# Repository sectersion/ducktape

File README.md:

# ducktape

**ducktape** is a budget-friendly, fully open alternative to the USB Rubber ducky, the well-known keystroke-injection tool used in cybersecurity and physical pentesting.  
The goal: COST OPTIMIZATION

Instead of hiding behind proprietary hardware, ducktape uses simple off-the-shelf parts and a dead-simple design you can understand, repair, and modify. Cheap to build, easy to hack on, and perfect for learning physical security without dropping triple digits on a dongle.

I built this because I’m diving deeper into physical access testing, and I refuse to pay luxury-brand prices for tools that are essentially microcontrollers pretending to be premium gear.  
Companies like Flipper and Hak5 make cool stuff — sure — but most of it can be recreated for a fraction of the price if you’re willing to solder and tinker.

## Schematic

## PCB

## 3D Model

## Disclaimer
This project is for **educational and authorized security testing only**.  
You’re responsible for how you use it.  
If you plug this into a device you don’t have explicit permission to test, that’s on you, not me, not the repo, not the PCB.

Pentest ethically.

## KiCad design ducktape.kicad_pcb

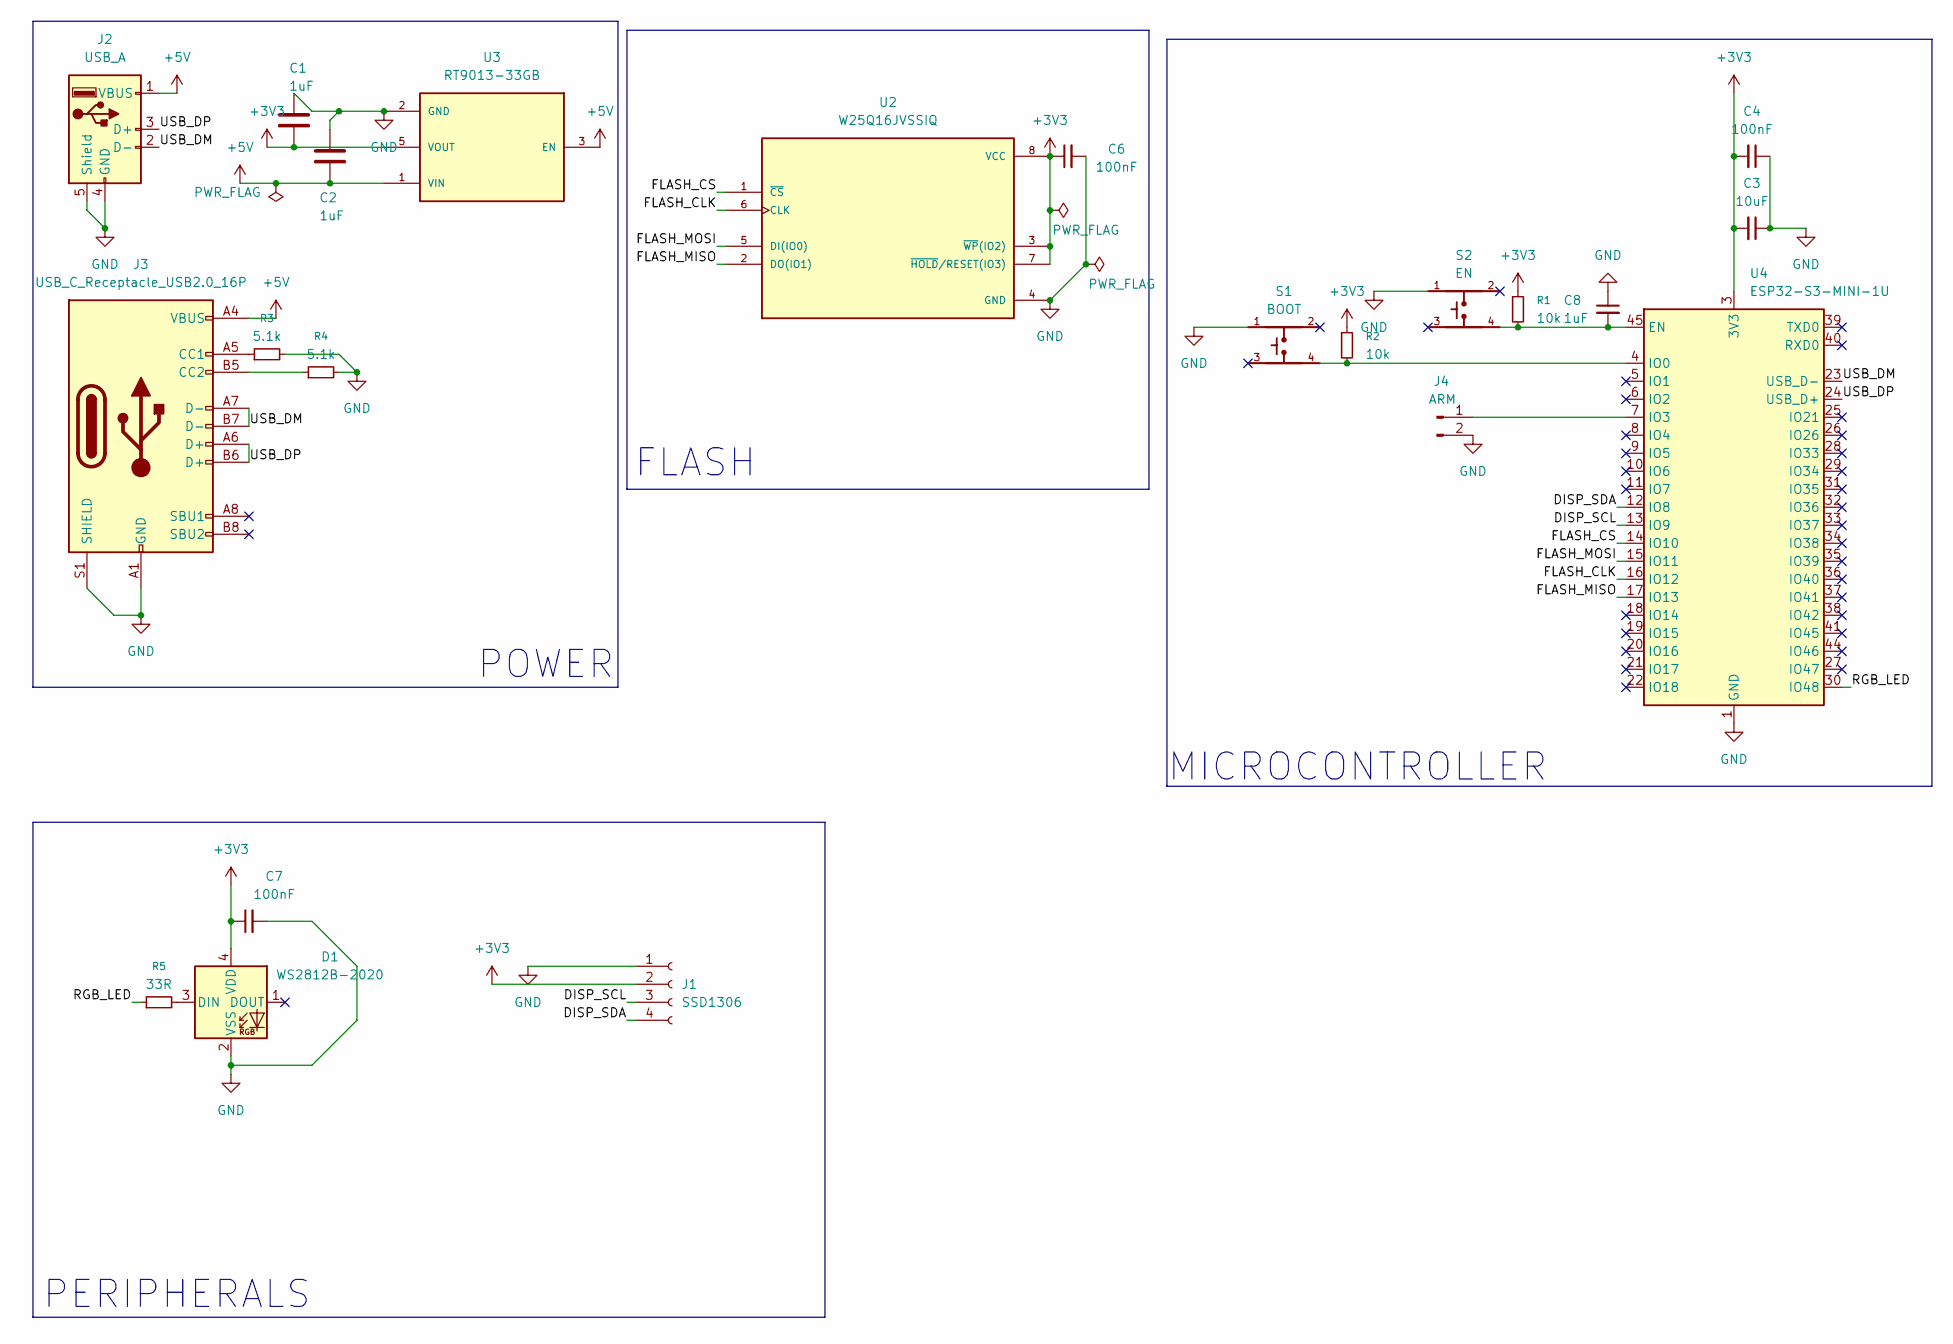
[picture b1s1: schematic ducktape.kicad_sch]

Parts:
C1, C2, C8: 1uF; C_0402_1005Metric
C3: 10uF; C_0402_1005Metric
C4, C6, C7: 100nF; C_0402_1005Metric
D1: WS2812B-2020; LED_WS2812B-2020_PLCC4_2.0x2.0mm
J1: SSD1306; PinSocket_1x04_P2.54mm_Vertical
J2: USB_A; USB_A_CNCTech_1001-011-01101_Horizontal
J3: USB_C_Receptacle_USB2.0_16P; USB_C_Receptacle_HRO_TYPE-C-31-M-12
J4: ARM; PinHeader_1x02_P2.54mm_Vertical
R1, R2: 10k; R_0402_1005Metric
R3, R4: 5.1k; R_0402_1005Metric
R5: 33R; R_0402_1005Metric
S1: BOOT; SW_SKRPACE010
S2: EN; SW_SKRPACE010
U2: W25Q16JVSSIQ; SOIC127P790X216-8N
U3: RT9013-33GB; SOT94P279X129-5N; PARTREV Aprill 2011
U4: ESP32-S3-MINI-1U; ESP32-S2-MINI-1U

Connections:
+3V3: C1.2, C3.2, C4.2, C6.1, C7.1, D1.4 (VDD), J1.2, R1.1, R2.1, U2.3 (~WP(IO2)), U2.7 (~HOLD/RESET(IO3)), U2.8 (VCC), U3.5 (VOUT), U4.3 (3V3)
+5V: C2.2, J2.1 (VBUS), J3.A4 (VBUS), J3.A9 (VBUS), J3.B4 (VBUS), J3.B9 (VBUS), U3.1 (VIN), U3.3 (EN)
/DISP_SCL: J1.3, U4.13 (IO9)
/DISP_SDA: J1.4, U4.12 (IO8)
/FLASH_CLK: U2.6 (CLK), U4.16 (IO12)
/FLASH_CS: U2.1 (~CS), U4.14 (IO10)
/FLASH_MISO: U2.2 (DO(IO1)), U4.17 (IO13)
/FLASH_MOSI: U2.5 (DI(IO0)), U4.15 (IO11)
/RGB_LED: R5.1, U4.30 (IO48)
/USB_DM: J2.2 (D-), J3.A7 (D-), J3.B7 (D-), U4.23 (USB_D-)
/USB_DP: J2.3 (D+), J3.A6 (D+), J3.B6 (D+), U4.24 (USB_D+)
GND: C1.1, C2.1, C3.1, C4.1, C6.2, C7.2, C8.1, D1.2 (VSS), J1.1, J2.4 (GND), J2.5 (Shield), J3.A1 (GND), J3.A12 (GND), J3.B1 (GND), J3.B12 (GND), J3.S1 (SHIELD), J4.2, R3.2, R4.2, S1.1, S2.1, U2.4 (GND), U3.2 (GND), U4.1 (GND), U4.2 (GND), U4.42 (GND), U4.43 (GND), U4.46 (GND), U4.47 (GND), U4.48 (GND), U4.49 (GND), U4.50 (GND), U4.51 (GND), U4.52 (GND), U4.53 (GND), U4.54 (GND), U4.55 (GND), U4.56 (GND), U4.57 (GND), U4.58 (GND), U4.59 (GND), U4.60 (GND), U4.61 (GND), U4.62 (GND), U4.63 (GND), U4.64 (GND), U4.65 (GND)
unnamed: D1.3 (DIN), R5.2
unnamed: J3.A5 (CC1), R3.1
unnamed: J3.B5 (CC2), R4.1
unnamed: J4.1, U4.7 (IO3)
unnamed: C8.2, R1.2, S2.4, U4.45 (EN)
unnamed: R2.2, S1.4, U4.4 (IO0)

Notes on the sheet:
PERIPHERALS
MICROCONTROLLER
POWER
FLASH

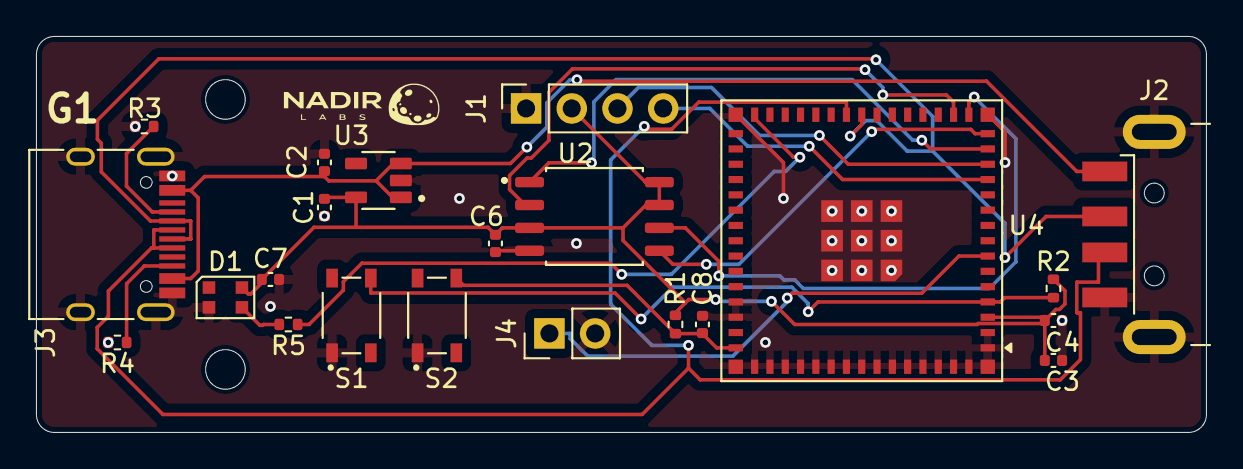
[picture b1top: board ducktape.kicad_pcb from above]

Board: 2 copper layers, 65.0 x 22.0 mm, 25 parts (0 on the bottom side), 18 nets.

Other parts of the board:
G1: LOGO; nl_bw
REF1, REF1#2: MountingHole_2.2mm_M2

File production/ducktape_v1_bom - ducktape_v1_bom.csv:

Designator,Footprint,Quantity,Value,LCSC Part #
"C1, C2, C8",0402,3,1uF,C14445
C3,0402,1,10uF,C315248
"C4, C6, C7",0402,3,100nF,C77020
D1,LED_WS2812B-2020_PLCC4_2.0x2.0mm,1,WS2812B-2020,C965555
J1,PinSocket_1x04_P2.54mm_Vertical,1,SSD1306,C2718488
J2,USB_A_CNCTech_1001-011-01101_Horizontal,1,USB_A,C2943127
J3,USB_C_Receptacle_HRO_TYPE-C-31-M-12,1,USB_C_Receptacle_USB2.0_16P,C165948
J4,PinHeader_1x02_P2.54mm_Vertical,1,ARM,C42431798
"R1, R2",0402,2,10k,C60490
"R3, R4",0402,2,5.1k,C105872
R5,0402,1,33R,C138002
S1,SW_SKRPACE010,1,BOOT,C139797
S2,SW_SKRPACE010,1,EN,C139797
U2,SOIC127P790X216-8N,1,W25Q16JVSSIQ,C131025
U3,SOT94P279X129-5N,1,RT9013-33GB,C47773
U4,ESP32-S2-MINI-1U,1,ESP32-S3-MINI-1U,C2980299

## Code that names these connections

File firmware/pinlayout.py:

from machine import Pin

# display pin assignments
DISP_SDA = Pin(8)   # data
DISP_SCL = Pin(9)   # clock

#flash pins
FLASH_CS = Pin(10)
FLASH_MOSI = Pin(11)
FLASH_CLK = Pin(12)
FLASH_MISO = Pin(13)

#led
RGB_LED = Pin(48)

#arm header
ARM = Pin(3, Pin.IN, Pin.PULL_UP)

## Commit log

2026-03-23 feat: schematic in one sitting
2026-03-24 finish pcb and generate gerbers
2026-03-25 finish PCB and export 3d model
2026-03-25 Create README.md for ducktape project
    Add README.md for ducktape project with details on its purpose, design, and usage.
2026-04-12 upload
2026-04-12 Enhance README with schematic and PCB details
    Added schematic and PCB sections with images to README.
